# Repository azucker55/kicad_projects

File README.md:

# kicad_projects
Repository for everything KiCAD

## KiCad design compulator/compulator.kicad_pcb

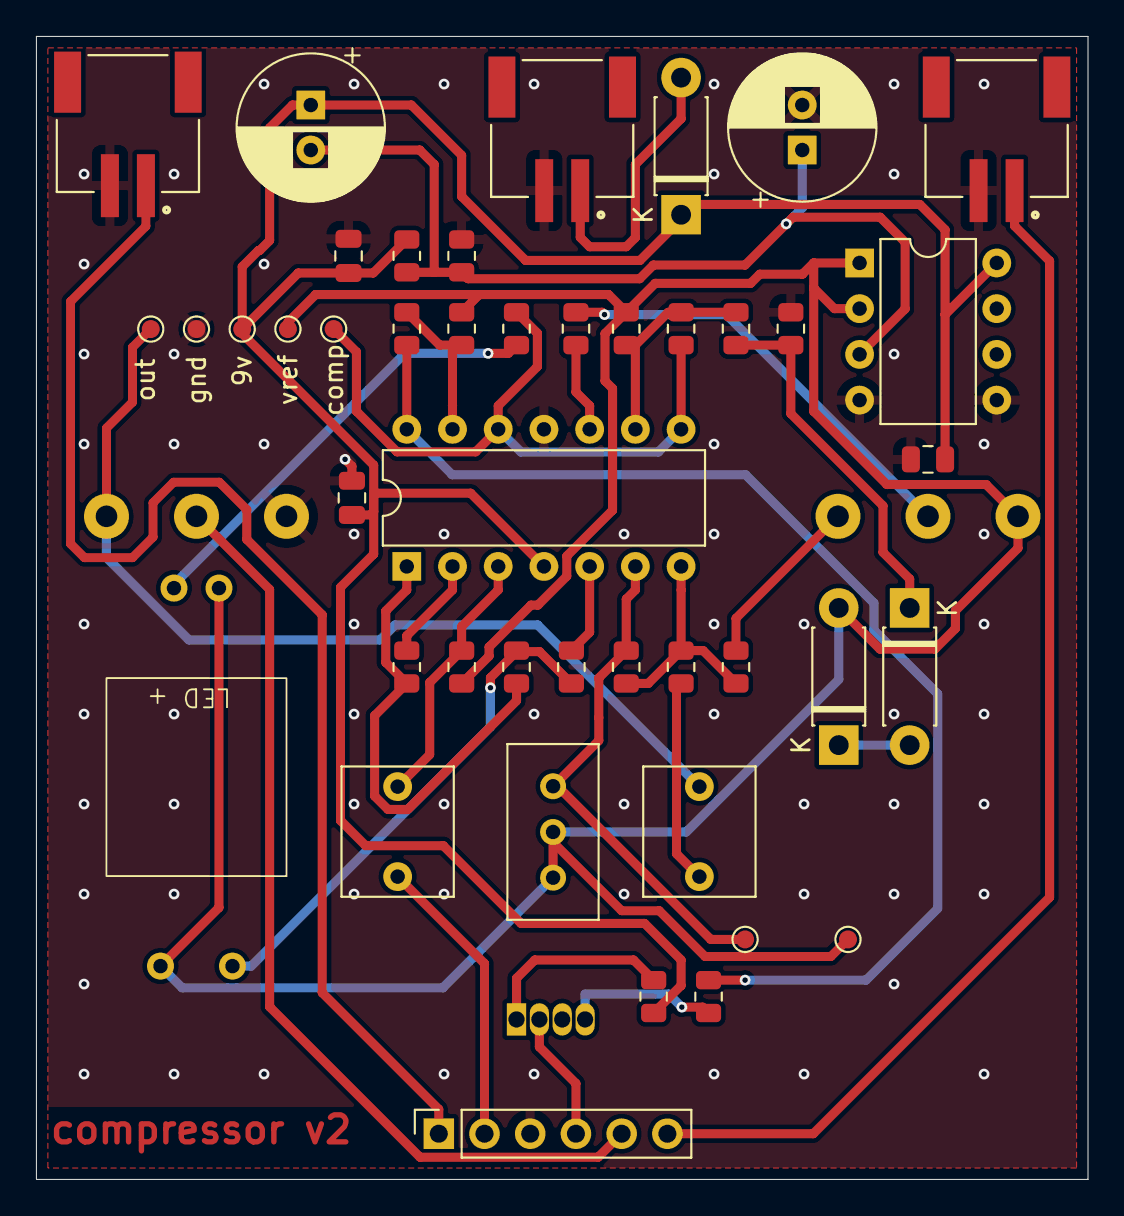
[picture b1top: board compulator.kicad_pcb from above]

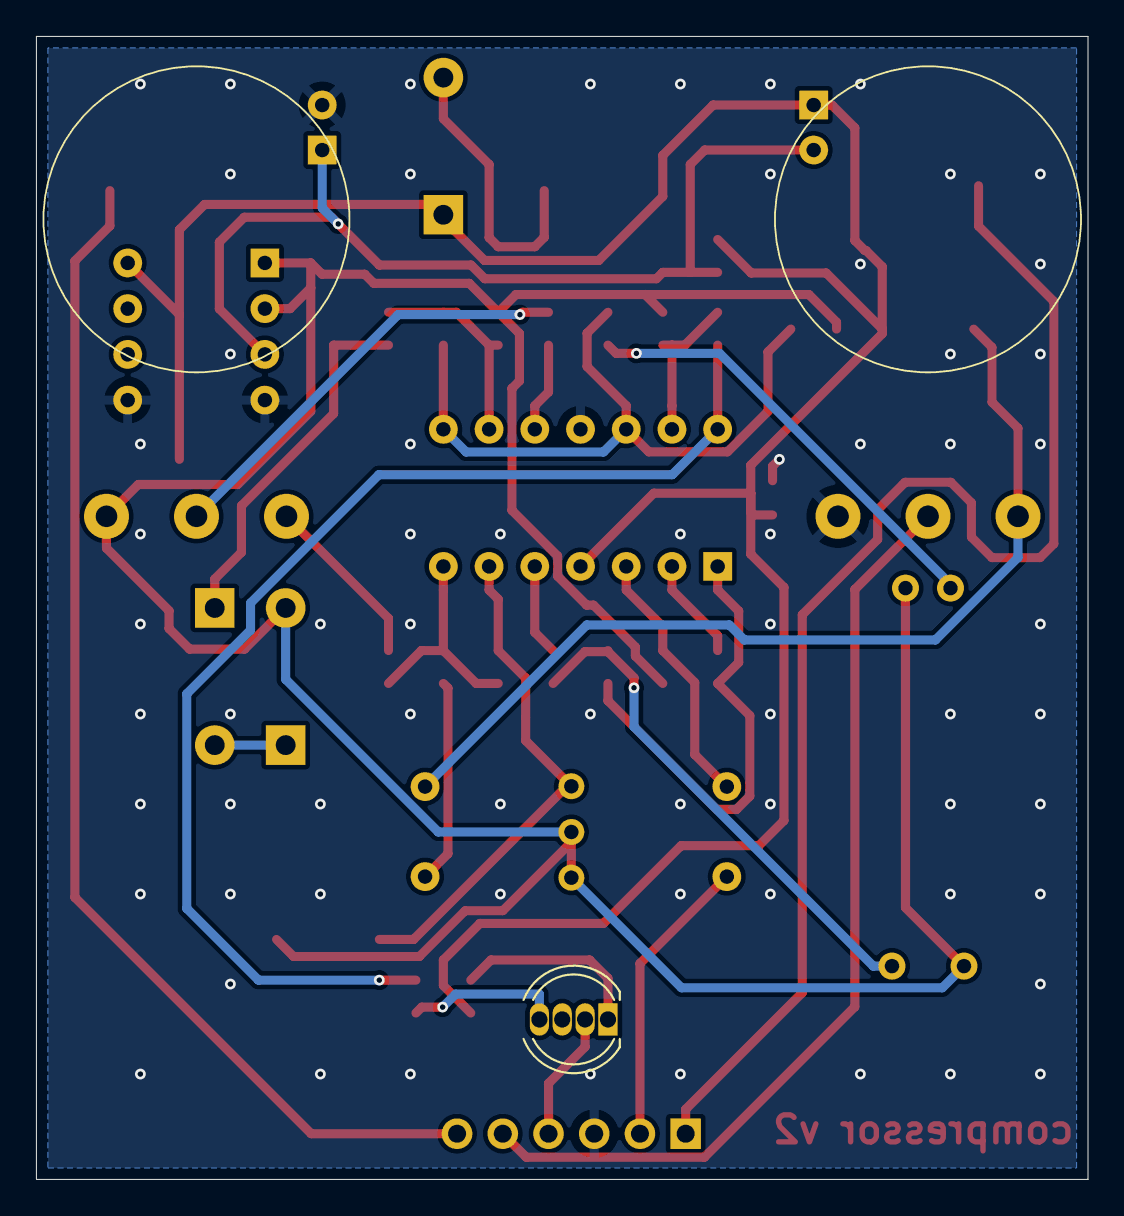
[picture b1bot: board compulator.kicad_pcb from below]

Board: 2 copper layers, 58.4 x 63.5 mm, 47 parts (3 on the bottom side), 32 nets.

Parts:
C1, C7, C8: 100n; C_0805_2012Metric
C3, C4: 4.7u; CP_Radial_D8.0mm_P2.50mm
C5, C6: 1u; C_Rect_L7.0mm_W6.0mm_P5.00mm
COMP1: 20k LOG; 16mm-pot
D1, D3, D4: 1N4148; D_DO-41_SOD81_P7.62mm_Horizontal
D2: LED_KRGB; LED_D5.0mm-4_RGB
J1, J2, J3: S2B-PH-SM4-TB_LF__SN_; JST_S2B-PH-SM4-TB_LF__SN_
J4: Conn_01x06; PinSocket_1x06_P2.54mm_Vertical
LDR1: LDR XVIVE VTL5C1
LEVEL1: 20k LOG; 16mm-pot
P1: 10k (2.4k); Potentiometer_Bourns_3296W_Vertical
R1, R4, R6, R7, R9, R14, R15, R16, R19: 10k; R_0805_2012Metric
R2, R3: 47k; R_0805_2012Metric
R5: 1M; R_0805_2012Metric
R8, R10, R11: 1k; R_0805_2012Metric
R12, R13: 680; R_0805_2012Metric
R17: 1.5k; R_0805_2012Metric
R18: 82k; R_0805_2012Metric
TP1: P11; TestPoint_Pad_D1.0mm
TP2: P22; TestPoint_Pad_D1.0mm
TP3: out; TestPoint_Pad_D1.0mm
TP4: comp; TestPoint_Pad_D1.0mm
TP5: vref; TestPoint_Pad_D1.0mm
TP6: 9v; TestPoint_Pad_D1.0mm
TP7: gnd; TestPoint_Pad_D1.0mm
U1: Opamp_Dual; DIP-8_W7.62mm
U4: TL074; DIP-14_W7.62mm

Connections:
+9V: C1.2 (-), C3.1 (+), C7.2 (-), C8.2 (-), D1.1 (K), R2.1 (+), R4.1 (+), TP6.1, U1.8 (V+), U4.4 (V+)
GNDA: C1.1 (+), C4.2 (-), C7.1 (+), C8.1 (+), J1.2, J2.2, J3.2, J4.3, LEVEL1.1, R3.2 (-), R16.2 (-), TP7.1, U1.4 (V-), U1.5 (+), U4.11 (V-)
IN: C5.1 (+), J4.2
J-IN: J2.1, J4.1
J-OUT: J3.1, J4.6
LED: D2.2 (K), J4.4
unnamed: C3.2 (-), C4.1 (+), R2.2 (-), R3.1 (+), U1.3 (+)
unnamed: C5.2 (-), R5.1 (+), U4.3 (+)
unnamed: C6.1 (+), R11.2 (-)
unnamed: C6.2 (-), LEVEL1.3, TP3.1
unnamed: D1.2 (A), J1.1
unnamed: D2.4 (BA), R1.2 (-)
unnamed: D2.1 (RA), R4.2 (-)
unnamed: D3.2 (A), D4.1 (K)
unnamed: D3.1 (K), R15.2 (-), R16.1 (+)
unnamed: P1.3 (c), R9.1 (+), TP2.1, U4.6 (-)
unnamed: R1.1 (+), R18.1 (+), U4.14
unnamed: R6.1 (+), U4.2 (-)
unnamed: R6.2 (-), R7.1 (+), U4.1
unnamed: LDR1.1, R7.2 (-), R8.1 (+)
unnamed: R8.2 (-), U4.5 (+)
unnamed: R9.2 (-), R10.1 (+), R11.1 (+), U4.7
unnamed: COMP1.3, R10.2 (-)
unnamed: R12.1 (+), U4.10 (+)
unnamed: COMP1.2, R12.2 (-)
unnamed: LDR1.4, R13.1 (+)
unnamed: R13.2 (-), R14.1 (+), TP4.1, U4.8, U4.12 (+)
unnamed: R14.2 (-), R15.1 (+), R17.2 (-), U4.9 (-)
unnamed: R18.2 (-), R19.1 (+), U4.13 (-)
unnamed: U1.6 (-), U1.7
OUT: J4.5, LEVEL1.2
VREF: COMP1.1, D4.2 (A), LDR1.2, LDR1.3, P1.1 (a), P1.2 (b), R5.2 (-), R17.1 (+), R19.2 (-), TP1.1, TP5.1, U1.1, U1.2 (-)

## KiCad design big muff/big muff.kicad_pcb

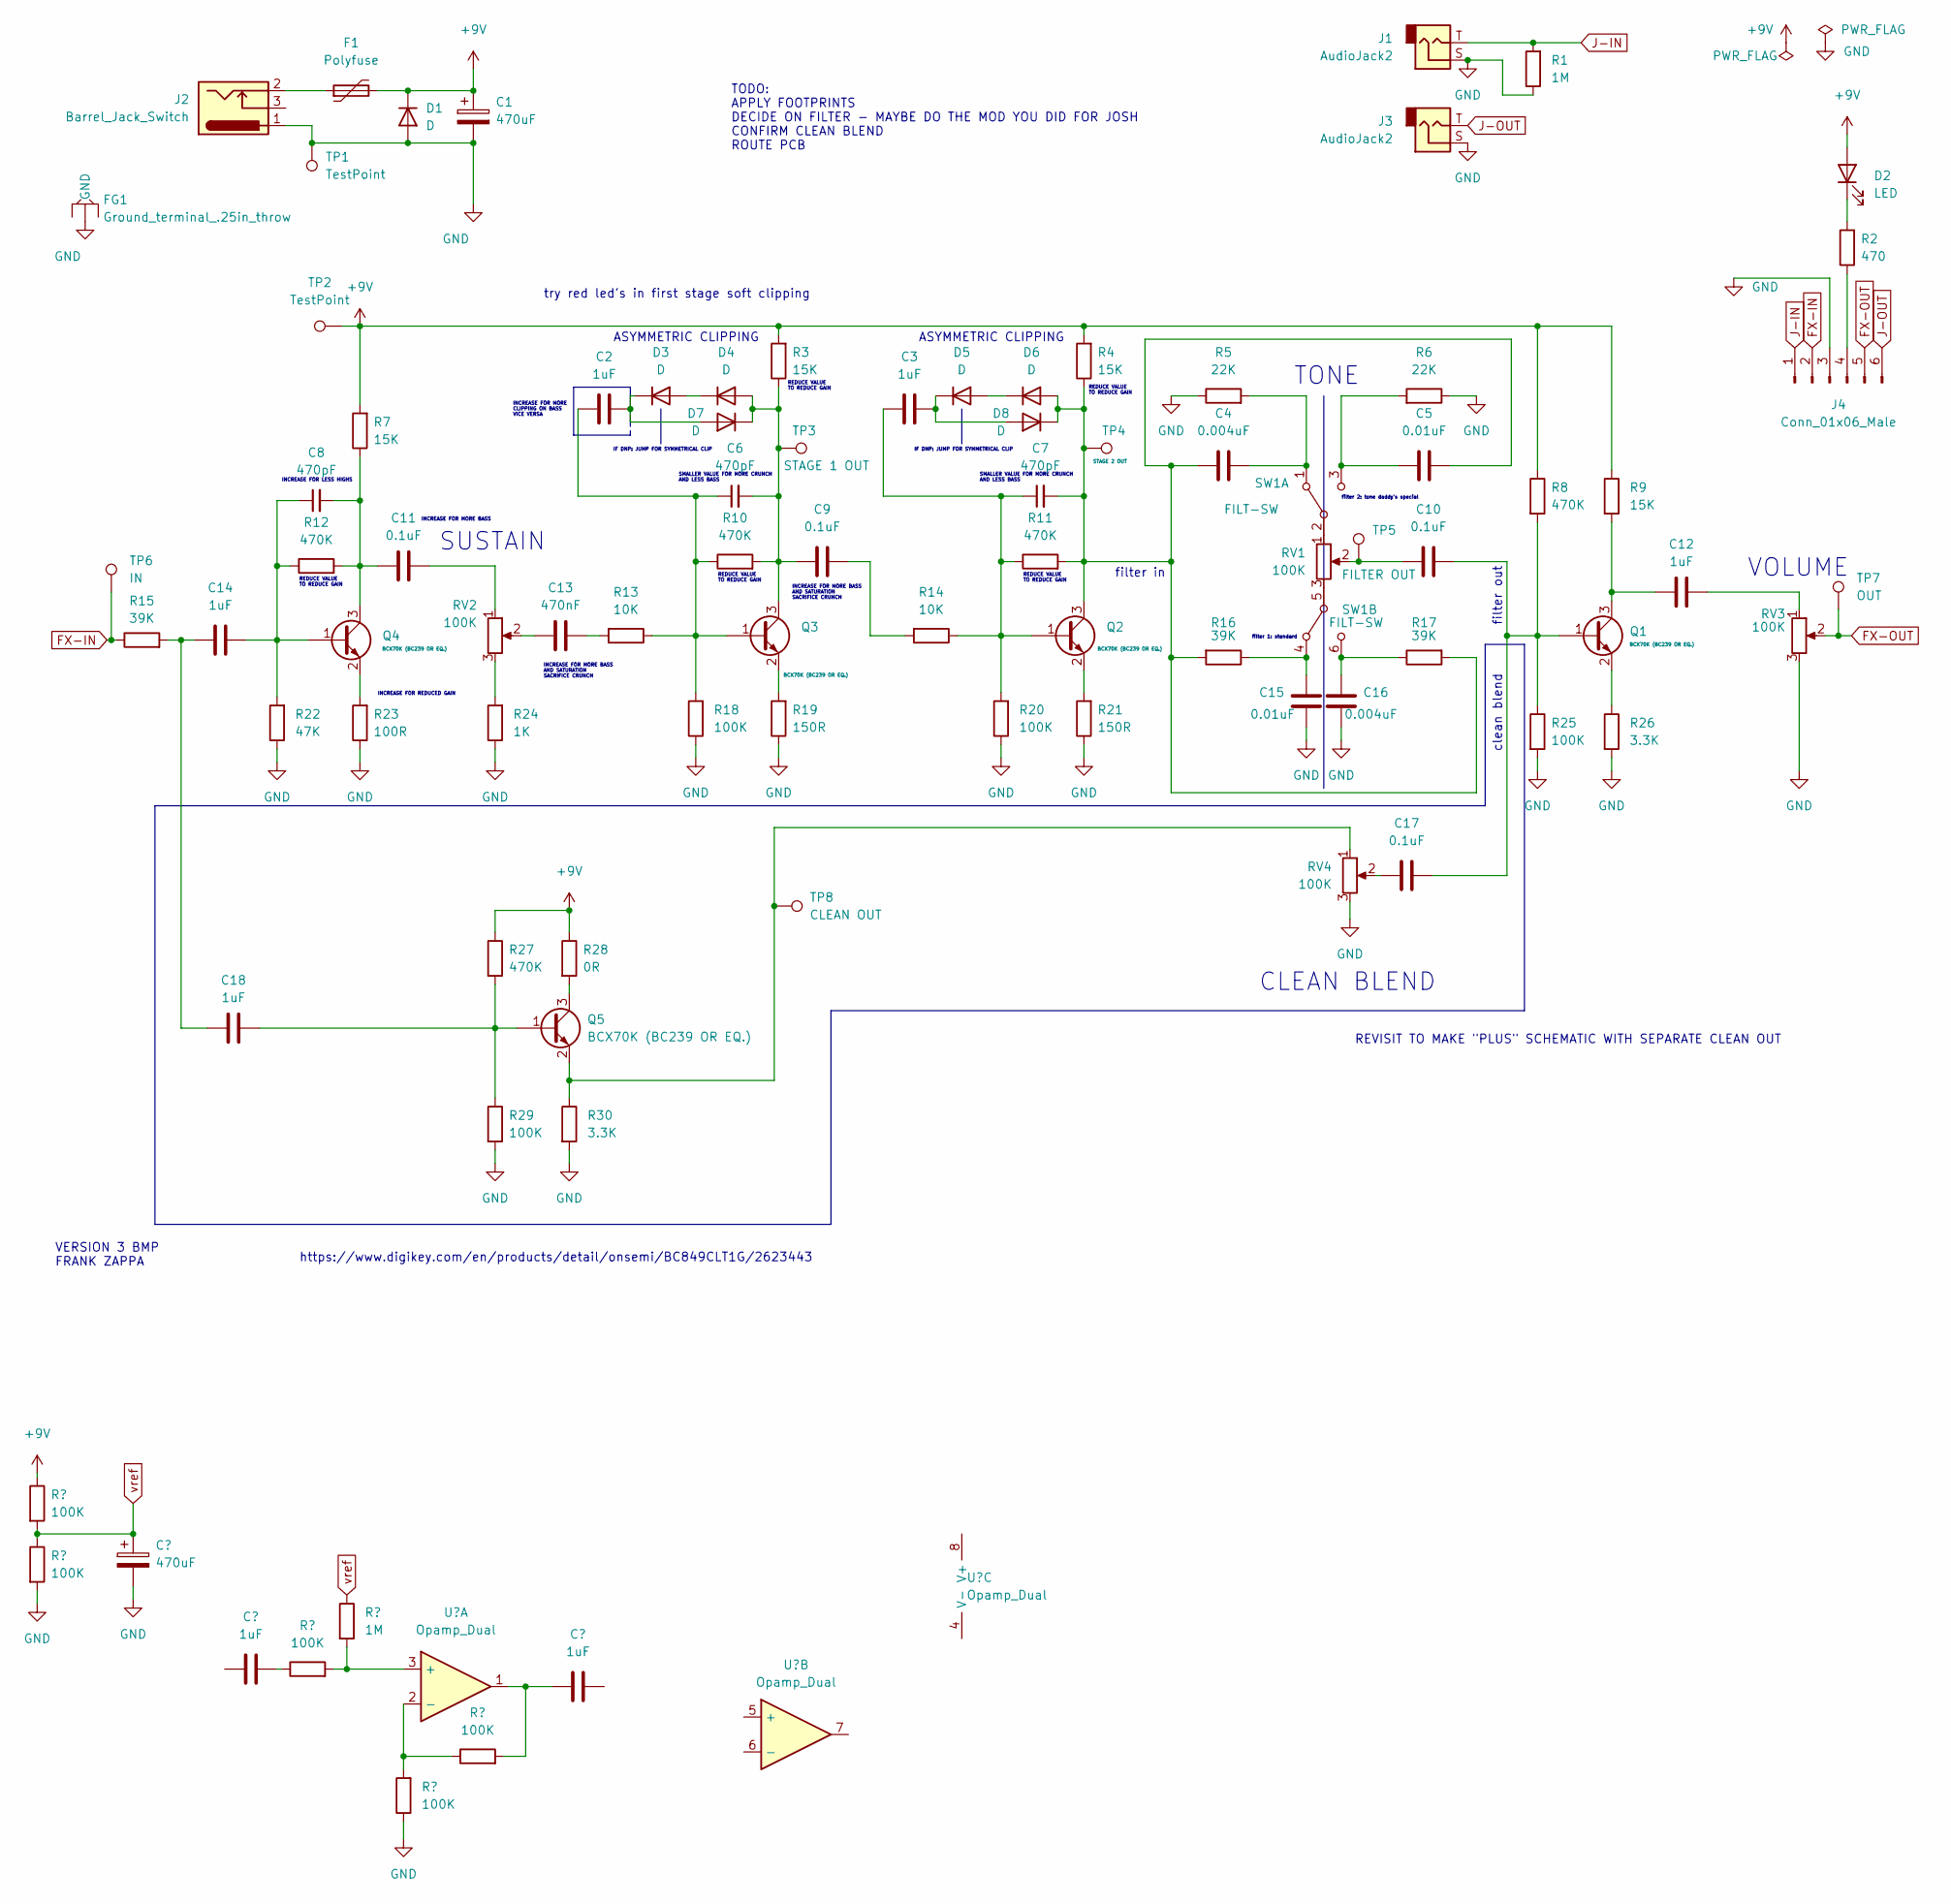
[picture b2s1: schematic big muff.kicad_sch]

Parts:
C1: 470uF; CP_Elec_6.3x5.7
C2, C3, C12, C14, C18: 1uF; C_1210_3225Metric
C4, C16: 0.004uF; C_0805_2012Metric
C5, C15: 0.01uF; C_0805_2012Metric
C6, C7, C8: 470pF; C_0805_2012Metric
C9, C10, C11, C17: 0.1uF; C_0805_2012Metric
C13: 470nF; C_1210_3225Metric
D1, D3, D4, D5, D6, D7, D8: D; D_SOD-123
D2: LED; LED_D5.0mm
F1: Polyfuse; Fuse_1206_3216Metric
FG1: Ground_terminal_.25in_throw; SPRING CONTACT KEYSTONE-629
J1, J3: AudioJack2; 4080009
J2: Barrel_Jack_Switch; BarrelJack_CUI_PJ-102AH_Horizontal
J4: Conn_01x06_Male; 1x06
Q1, Q2, Q3, Q4, Q5: BCX70K (BC239 OR EQ.); SOT-23
R1: 1M; R_0805_2012Metric
R2: 470; R_0805_2012Metric
R3, R4, R7, R9: 15K; R_0805_2012Metric
R5, R6: 22K; R_0805_2012Metric
R8, R10, R11, R12, R27: 470K; R_0805_2012Metric
R13, R14: 10K; R_0805_2012Metric
R15, R16, R17: 39K; R_0805_2012Metric
R18, R20, R25, R29: 100K; R_0805_2012Metric
R19, R21: 150R; R_0805_2012Metric
R22: 47K; R_0805_2012Metric
R23: 100R; R_0805_2012Metric
R24: 1K; R_0805_2012Metric
R26, R30: 3.3K; R_0805_2012Metric
R28: 0R; R_0805_2012Metric
RV1, RV2, RV3, RV4: 100K; 16MM POT STANDARD
SW1: FILT-SW; DPDT_GRAYHILL-78K01T
TP1, TP2: TestPoint; TestPoint_Loop_D1.80mm_Drill1.0mm_Beaded
TP3: STAGE 1 OUT; TestPoint_Loop_D1.80mm_Drill1.0mm_Beaded
TP4: STAGE 2 OUT; TestPoint_Loop_D1.80mm_Drill1.0mm_Beaded
TP5: FILTER OUT; TestPoint_Loop_D1.80mm_Drill1.0mm_Beaded
TP6: IN; TestPoint_Loop_D1.80mm_Drill1.0mm_Beaded
TP7: OUT; TestPoint_Loop_D1.80mm_Drill1.0mm_Beaded
TP8: CLEAN OUT; TestPoint_Loop_D1.80mm_Drill1.0mm_Beaded

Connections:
+9V: C1.1, D1.1 (K), D2.2 (A), F1.2, R3.2, R4.2, R7.2, R8.1, R9.1, R27.1, R28.1, TP2.1; also elsewhere on the board
FX-IN: J4.2, R15.1, TP6.1
FX-OUT: J4.5, RV3.2, TP7.1
GND: C1.2, C15.1, C16.1, D1.2 (A), FG1.1, J1.S, J2.1, J3.S, J4.3, R1.1, R5.1, R6.1, R18.1, R19.1, R20.1, R21.1, R22.1, R23.1, R24.1, R25.2, R26.2, R29.2, R30.2, RV3.3, RV4.3, TP1.1; also elsewhere on the board
J-IN: J1.T, J4.1, R1.2
J-OUT: J3.T, J4.6
unnamed: C9.2, R14.2
unnamed: C10.1, RV1.2, TP5.1
unnamed: C11.2, RV2.1
unnamed: C12.2, RV3.1
unnamed: C13.1, RV2.2
unnamed: C13.2, R13.2
unnamed: C14.1, C18.1, R15.2
unnamed: C17.1, RV4.2
unnamed: D2.1 (K), R2.2
unnamed: D3.2 (A), D4.1 (K)
unnamed: C2.2, D3.1 (K), D7.2 (A)
unnamed: C6.2, C9.1, D4.2 (A), D7.1 (K), Q3.3 (C), R3.1, R10.2, TP3.1
unnamed: D5.2 (A), D6.1 (K)
unnamed: C3.2, D5.1 (K), D8.2 (A)
unnamed: C4.1, C5.1, C7.2, D6.2 (A), D8.1 (K), Q2.3 (C), R4.1, R11.2, R16.2, R17.2, TP4.1
unnamed: F1.1, J2.2
unnamed: J4.4, R2.1
unnamed: C10.2, C17.2, Q1.1 (B), R8.2, R25.1
unnamed: C12.1, Q1.3 (C), R9.2
unnamed: Q1.2 (E), R26.1
unnamed: C3.1, C7.1, Q2.1 (B), R11.1, R14.1, R20.2
unnamed: Q2.2 (E), R21.2
unnamed: C2.1, C6.1, Q3.1 (B), R10.1, R13.1, R18.2
unnamed: Q3.2 (E), R19.2
unnamed: C8.1, C14.2, Q4.1 (B), R12.1, R22.2
unnamed: C8.2, C11.1, Q4.3 (C), R7.1, R12.2
unnamed: Q4.2 (E), R23.2
unnamed: C18.2, Q5.1 (B), R27.2, R29.1
unnamed: Q5.3 (C), R28.2
unnamed: Q5.2 (E), R30.1, RV4.1, TP8.1
unnamed: R24.2, RV2.3
unnamed: C4.2, R5.2, SW1.1 (A)
unnamed: RV1.1, SW1.2 (B)
unnamed: C5.2, R6.2, SW1.3 (C)
unnamed: C15.2, R16.1, SW1.4 (A)
unnamed: RV1.3, SW1.5 (B)
unnamed: C16.2, R17.1, SW1.6 (C)

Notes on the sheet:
INCREASE FOR REDUCED GAIN
INCREASE FOR MORE BASS
INCREASE FOR MORE BASS AND SATURATION SACRIFICE CRUNCH
REDUCE VALUE TO REDUCE GAIN
IF DNP: JUMP FOR SYMMETRICAL CLIP
VERSION 3 BMP FRANK ZAPPA
INCREASE FOR MORE CLIPPING ON BASS VICE VERSA
filter in
REVISIT TO MAKE "PLUS" SCHEMATIC WITH SEPARATE CLEAN OUT
VOLUME
INCREASE FOR LESS HIGHS
SMALLER VALUE FOR MORE CRUNCH AND LESS BASS
filter 1: standard
filter 2: tone daddy's special
CLEAN BLEND
ASYMMETRIC CLIPPING
TODO: APPLY FOOTPRINTS DECIDE ON FILTER - MAYBE DO THE MOD YOU DID FOR JOSH CONFIRM CLEAN BLEND ROUTE PCB
clean blend
SUSTAIN
TONE
try red led's in first stage soft clipping
filter out
https://www.digikey.com/en/products/detail/onsemi/BC849CLT1G/2623443

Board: 2 copper layers, 85 parts (5 on the bottom side), 45 nets, no tracks yet.

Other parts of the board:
C19: 470uF; CP_Elec_6.3x5.7
C20, C21: 1uF; C_1210_3225Metric
R31, R32, R33, R35, R36: 100K; R_0805_2012Metric
R34: 1M; R_0805_2012Metric

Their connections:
+9V: R31.1; also elsewhere on the board
GND: C19.2, R32.2, R35.1; also elsewhere on the board
unnamed: C20.2, R33.1
unnamed: C21.1, R36.2
unnamed: R33.2, R34.2
unnamed: R35.2, R36.1
vref: C19.1, R31.2, R32.1, R34.1

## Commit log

2025-03-30 add compulator (compressor project) v1
2025-03-30 update pcb save version
2025-03-30 add 3pdt true bypass project
2025-03-30 add big-muff project
2025-04-01 modified test pad names, flipped LED to bottom
2025-04-01 plot gerbers v2
